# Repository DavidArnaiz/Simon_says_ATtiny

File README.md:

# Simon_says_ATtiny

Simon game on ATtiny45/85 microcontroller

Simon_says_ATtiny is a simple project implementing the Simon game on a PCB controlled from a ATtiny45/85. 
The ATtiny is programed from the Arduino IDE.

Repository contents:
--------------------

 +) Documentation: BOM file, Technical specification, drawings...
 
 +) Hardware: Kicad project files, schematic in PDF and Gerber files
 
 +) Firmware: Arduino code.

Game description:
-----------------
Simon (Simon says) game is an electronic game created by Ralph H. Baer and Howard J. Morrison and it has been available since 1970. The game has four lights (typically red, green, yellow and blue) and four buttons. Each light has one button and one sound, generally a tone, linked to it. The game has two main phases:

  +) Sequence display: during this phase “Simon”, the game, will show the sequence you have to memorize. The sequence is shown by turning the lights one at a time until the sequence is completed. Throughout this phase the corresponding tones linked to the lights will also be played to serve as a memory aid.
  
  +) Copying phase: in this phase the player has to copy the sequence in the same order as displayed previously. To copy the sequence the player has to press the corresponding button linked to the light or tone it needs to copy. If there is a mistake while completing the sequence the game will end at that point.
  
These two sequences are repeated over and over increasing the sequence length until either the player louses or the maximum length sequence is reached. The game starts with a sequence of only length one and its length is increased adding one extra step to the current sequence.

Acknowledgments
----------------

For this project to work I'm using the Arduino core created by SpenceKonde:

https://github.com/SpenceKonde/ATTinyCore

Arduino community (Arduino IDE available there):

https://www.arduino.cc/

[The rest of attributions will be on the technical specification document]

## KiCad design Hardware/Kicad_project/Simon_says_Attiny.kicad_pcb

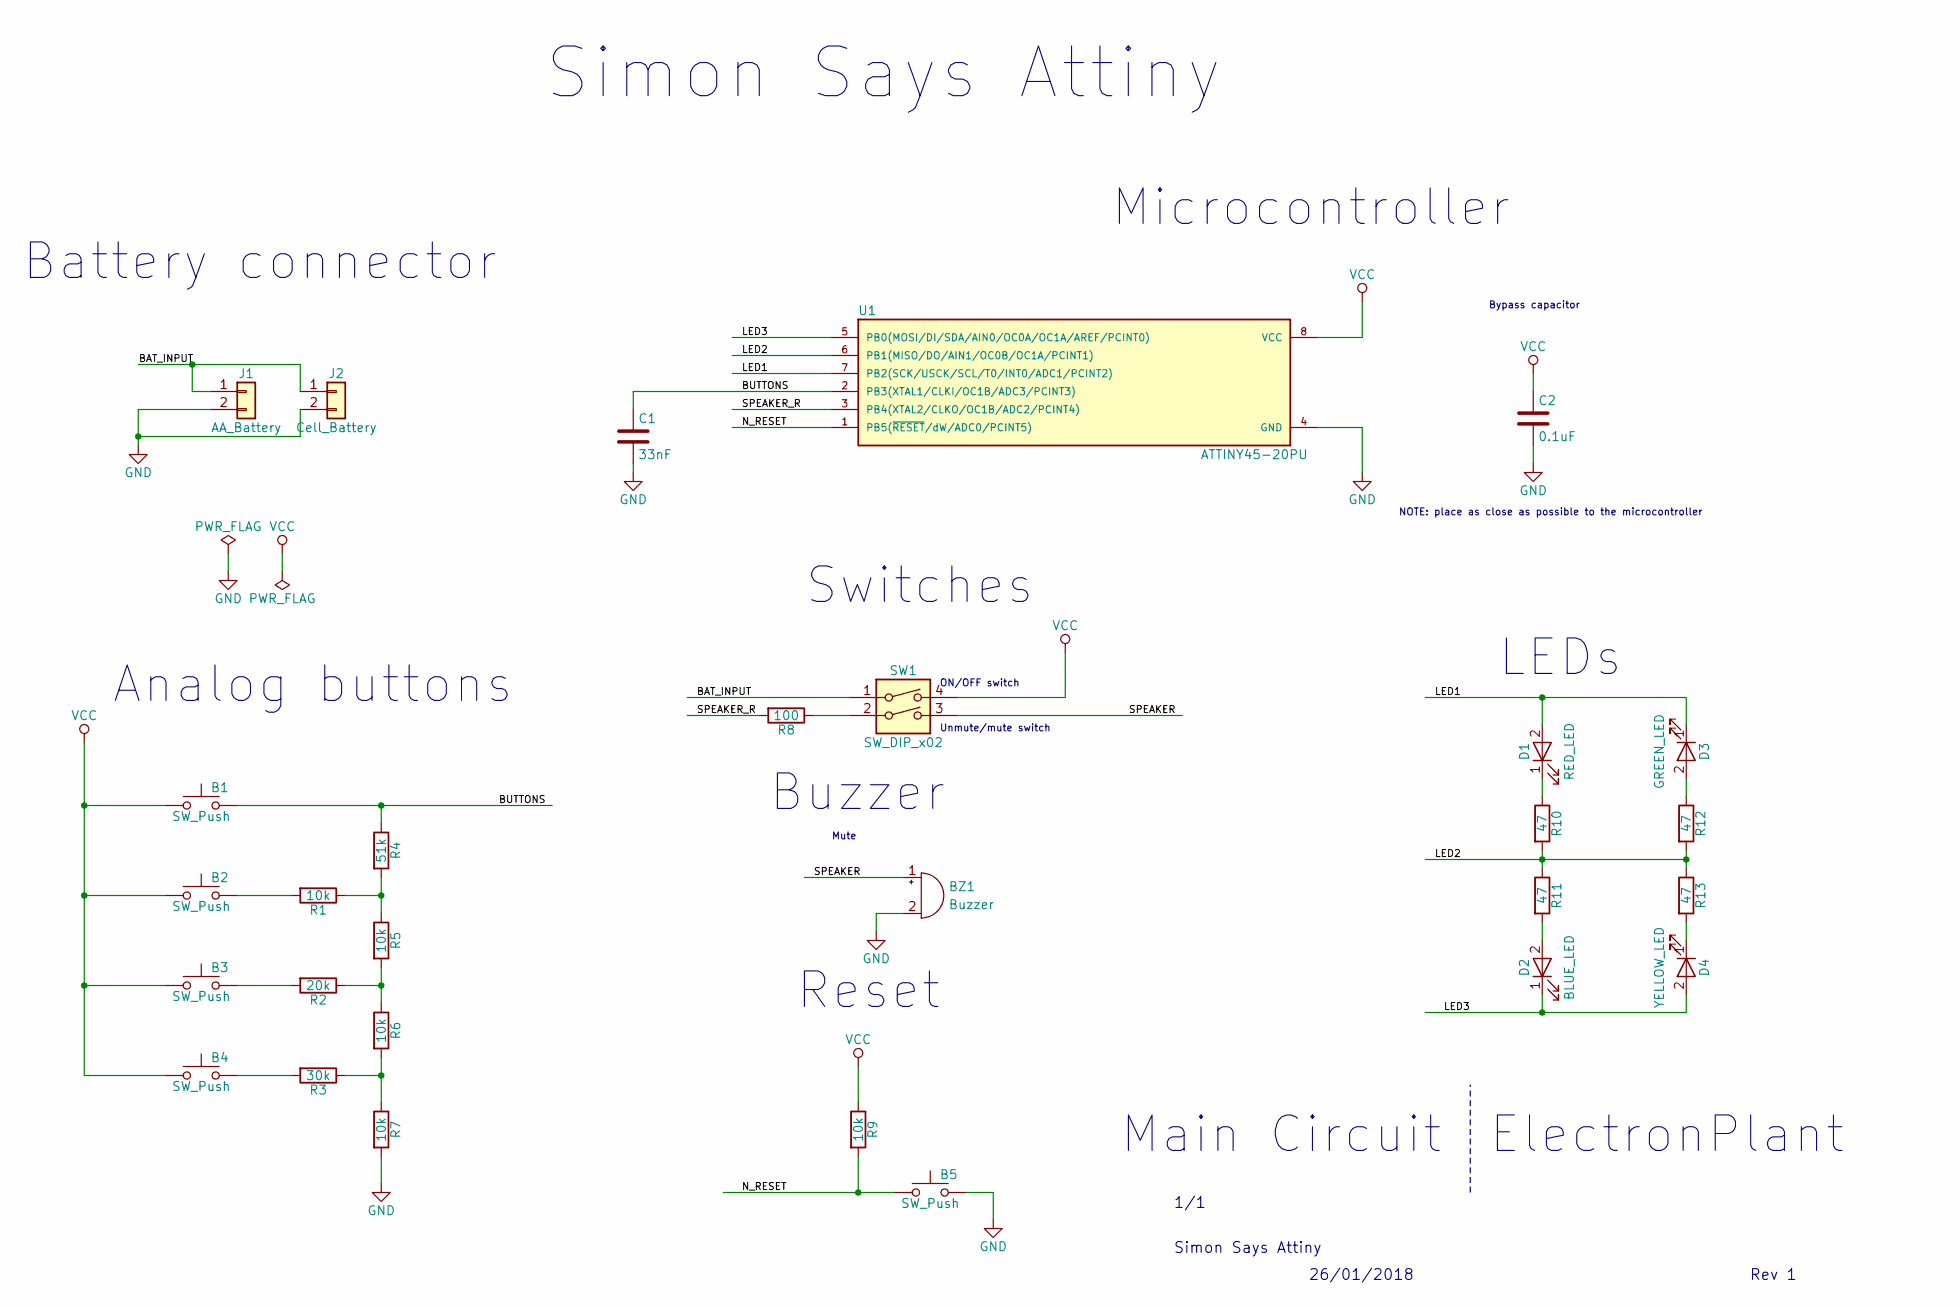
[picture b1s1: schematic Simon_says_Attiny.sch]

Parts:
B1, B2, B3, B4, B5: SW_Push; SW_PUSH_6mm
BZ1: Buzzer; Buzzer_12x9.5RM7.6
C1: 33nF; C_0805_HandSoldering
C2: 0.1uF; C_0805_HandSoldering
D1: RED_LED; LED_D5.0mm
D2: BLUE_LED; LED_D5.0mm
D3: GREEN_LED; LED_D5.0mm
D4: YELLOW_LED; LED_D5.0mm
J1: AA_Battery; Pin_Header_Straight_1x02_Pitch1.27mm
J2: Cell_Battery; Keystone_103_1x20mm-CoinCell
R1, R5, R6, R7, R9: 10k; R_0805_HandSoldering
R2: 20k; R_0805_HandSoldering
R3: 30k; R_0805_HandSoldering
R4: 51k; R_0805_HandSoldering
R8: 100; R_0805_HandSoldering
R10, R11, R12, R13: 47; R_0805_HandSoldering
SW1: SW_DIP_x02; SW_DIP_x2_W7.62mm_Slide
U1: ATTINY45-20PU; DIP-8_W7.62mm

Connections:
/BAT_INPUT: J1.1, J2.1, SW1.1
/BUTTONS: B1.2, C1.1, R4.1, U1.2 (PB3(XTAL1/CLKI/OC1B/ADC3/PCINT3))
/LED1: D1.2 (A), D3.1 (K), U1.7 (PB2(SCK/USCK/SCL/T0/INT0/ADC1/PCINT2))
/LED2: R10.2, R11.1, R12.2, R13.1, U1.6 (PB1(MISO/DO/AIN1/OC0B/OC1A/PCINT1))
/LED3: D2.1 (K), D4.2 (A), U1.5 (PB0(MOSI/DI/SDA/AIN0/OC0A/OC1A/AREF/PCI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)
/N_RESET: B5.1, R9.2, U1.1 (PB5(~RESET~/dW/ADC0/PCINT5))
/SPEAKER: BZ1.1 (-), SW1.3
/SPEAKER_R: R8.2, U1.3 (PB4(XTAL2/CLKO/OC1B/ADC2/PCINT4))
GND: B5.2, BZ1.2 (+), C1.2, C2.2, J1.2, J2.2, R7.2, U1.4 (GND)
unnamed: B2.2, R1.2
unnamed: B3.2, R2.2
unnamed: B4.2, R3.2
unnamed: D1.1 (K), R10.1
unnamed: D2.2 (A), R11.2
unnamed: D3.2 (A), R12.1
unnamed: D4.1 (K), R13.2
unnamed: R1.1, R4.2, R5.1
unnamed: R2.1, R5.2, R6.1
unnamed: R3.1, R6.2, R7.1
unnamed: R8.1, SW1.2
VCC: B1.1, B2.1, B3.1, B4.1, C2.1, R9.1, SW1.4, U1.8 (VCC)

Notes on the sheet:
Simon Says Attiny
26/01/2018
Rev 1
1/1
ElectronPlant
Main Circuit
Microcontroller
Bypass capacitor
NOTE: place as close as possible to the microcontroller
Buzzer
Analog buttons
Reset
LEDs
Battery connector
ON/OFF switch
Mute
Simon Says Attiny
Unmute/mute switch
Switches

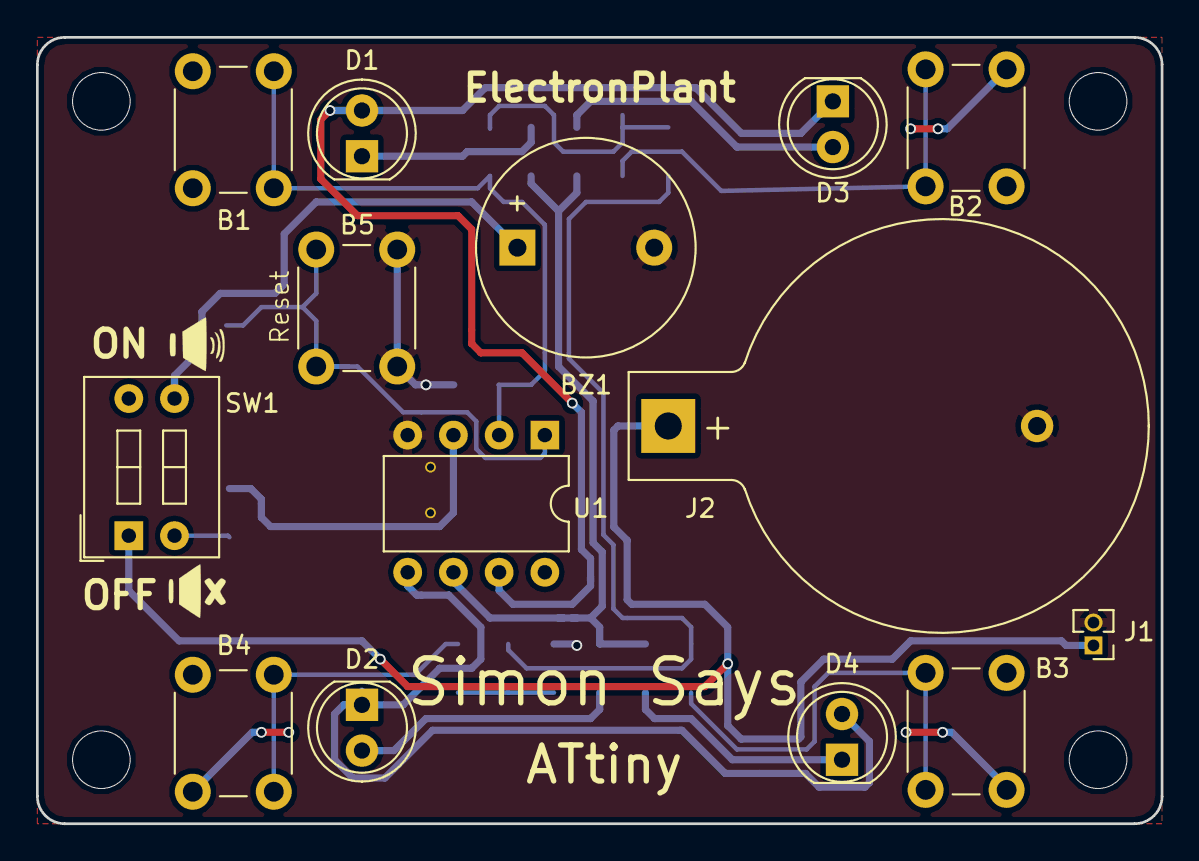
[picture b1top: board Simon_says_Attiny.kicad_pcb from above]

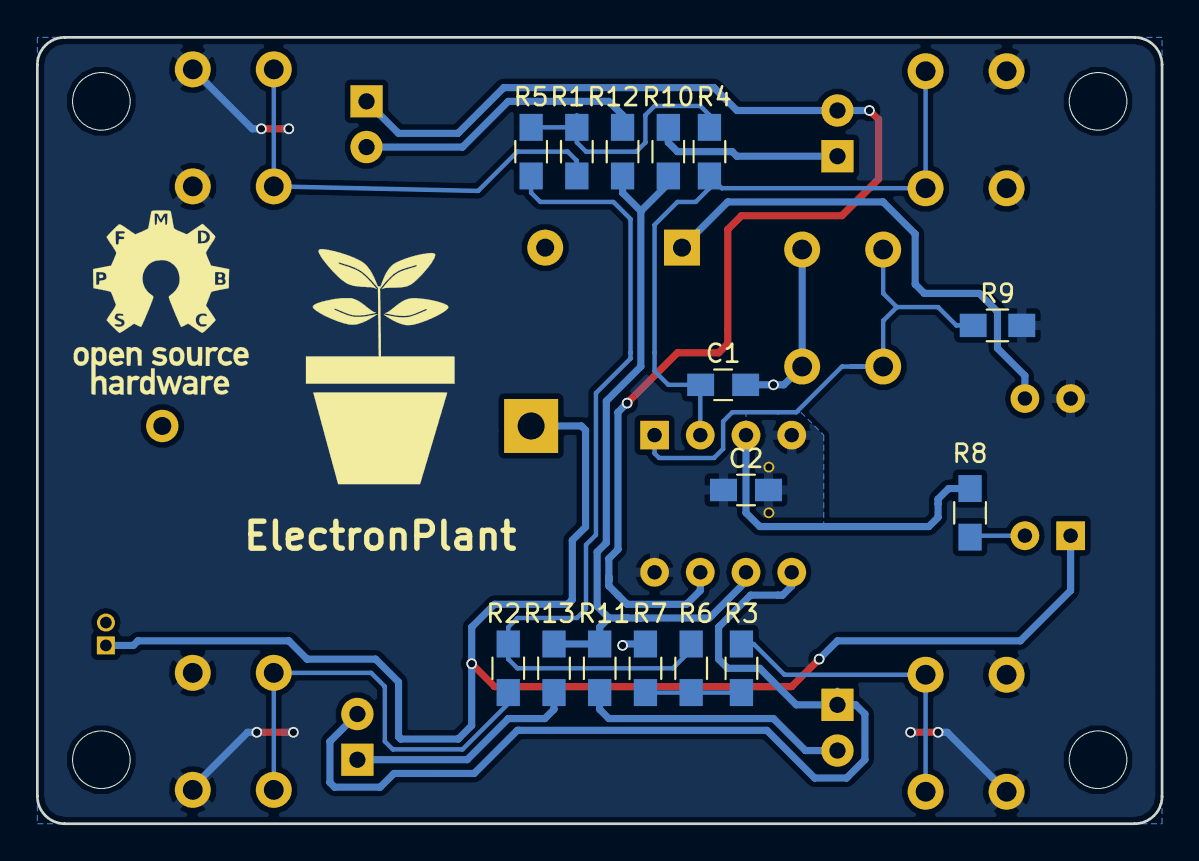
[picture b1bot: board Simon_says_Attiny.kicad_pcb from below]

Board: 2 copper layers, 62.5 x 43.7 mm, 29 parts (15 on the bottom side), 21 nets.

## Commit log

2018-03-04 License corrected.
    The license change to have the typical OSH license
2018-03-04 License file extension added
2018-03-04 Modifications on the license
    Small corrections as it didn't look ok in the browser
2018-03-04 Missing link added
    So many changes xd....
2018-03-04 Description Added
2018-03-04 Format corrected
    -_- wrong format again
2018-03-04 Image added
    Just testing
2018-03-04 Image corrected
2018-03-04 Image added + description
    Lets see if I can do it in 1 commit
2018-03-04 Format corrected
    Almost :'(
2018-03-04 Image corrected
    ... no comments
2018-03-04 Test
2018-03-04 Test2
2018-03-04 Test3
2018-03-04 Image
2018-03-13 Code Added
    .ino code added
2018-03-14 files added
    Code --> comment correction
    Harware files uploaded
    :)
2018-03-14 BOM added
    Added the BOM file
2018-03-14 BOM corrected
2018-11-11 BOM and Schematics corrected
    PDF files replaced by their new version
2018-11-11 Schematics correction
    The PDF didn't generate correctly :(
